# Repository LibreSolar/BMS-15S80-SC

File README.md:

# BMS48V
Battery management system for up to 15 Li-ion cells based on bq76940 or bq76930 IC from Texas Instruments

Please find a good description about system integration of the BMS in the [Open Source Ecology Wiki](https://wiki.opensourceecology.de/24-48V_BMS) (in German).

## Features (updated version 03/2022):
- implemented new plug (Würth 66202021022) to connect accumulator cells to PCB. This modification was necessary in order to ensure correct behaviour of measuring the cell voltage with BQ76940. Cell tap number C10 was dividied into C10/C10.1 and C5 into C5/C5.1.
- correct connection of CAN IC
- adapt board dimension to fit into following cap rail casing:
Apra Rail F06 open or M06 open 107*90*48 mm

ordering for example here:
https://www.reichelt.de/leergehaeuse-db6-fmh-
90-x-107-x-33-mm-apra-fo6-o-p251001.html?
&trstct=pos_3&nbc=1

## Features (updated version 10/2016):

- Up to 15 Li-ion cells (e.g. LiFePO4)
- Power circuit on separate board (see Switch-N-Sense repository)
- Balancing current approx. 150 mA
- STM32F072 ARM Cortex M0 microcontroller
- Built-in CAN communication interface and UEXT extension connector

## History

- Previous version was compatible to Arduino (based on ATmega 328P), but the processor was too small and didn't support CAN --> switched to STM32F072

(you can still find the old version by going back in the repository)

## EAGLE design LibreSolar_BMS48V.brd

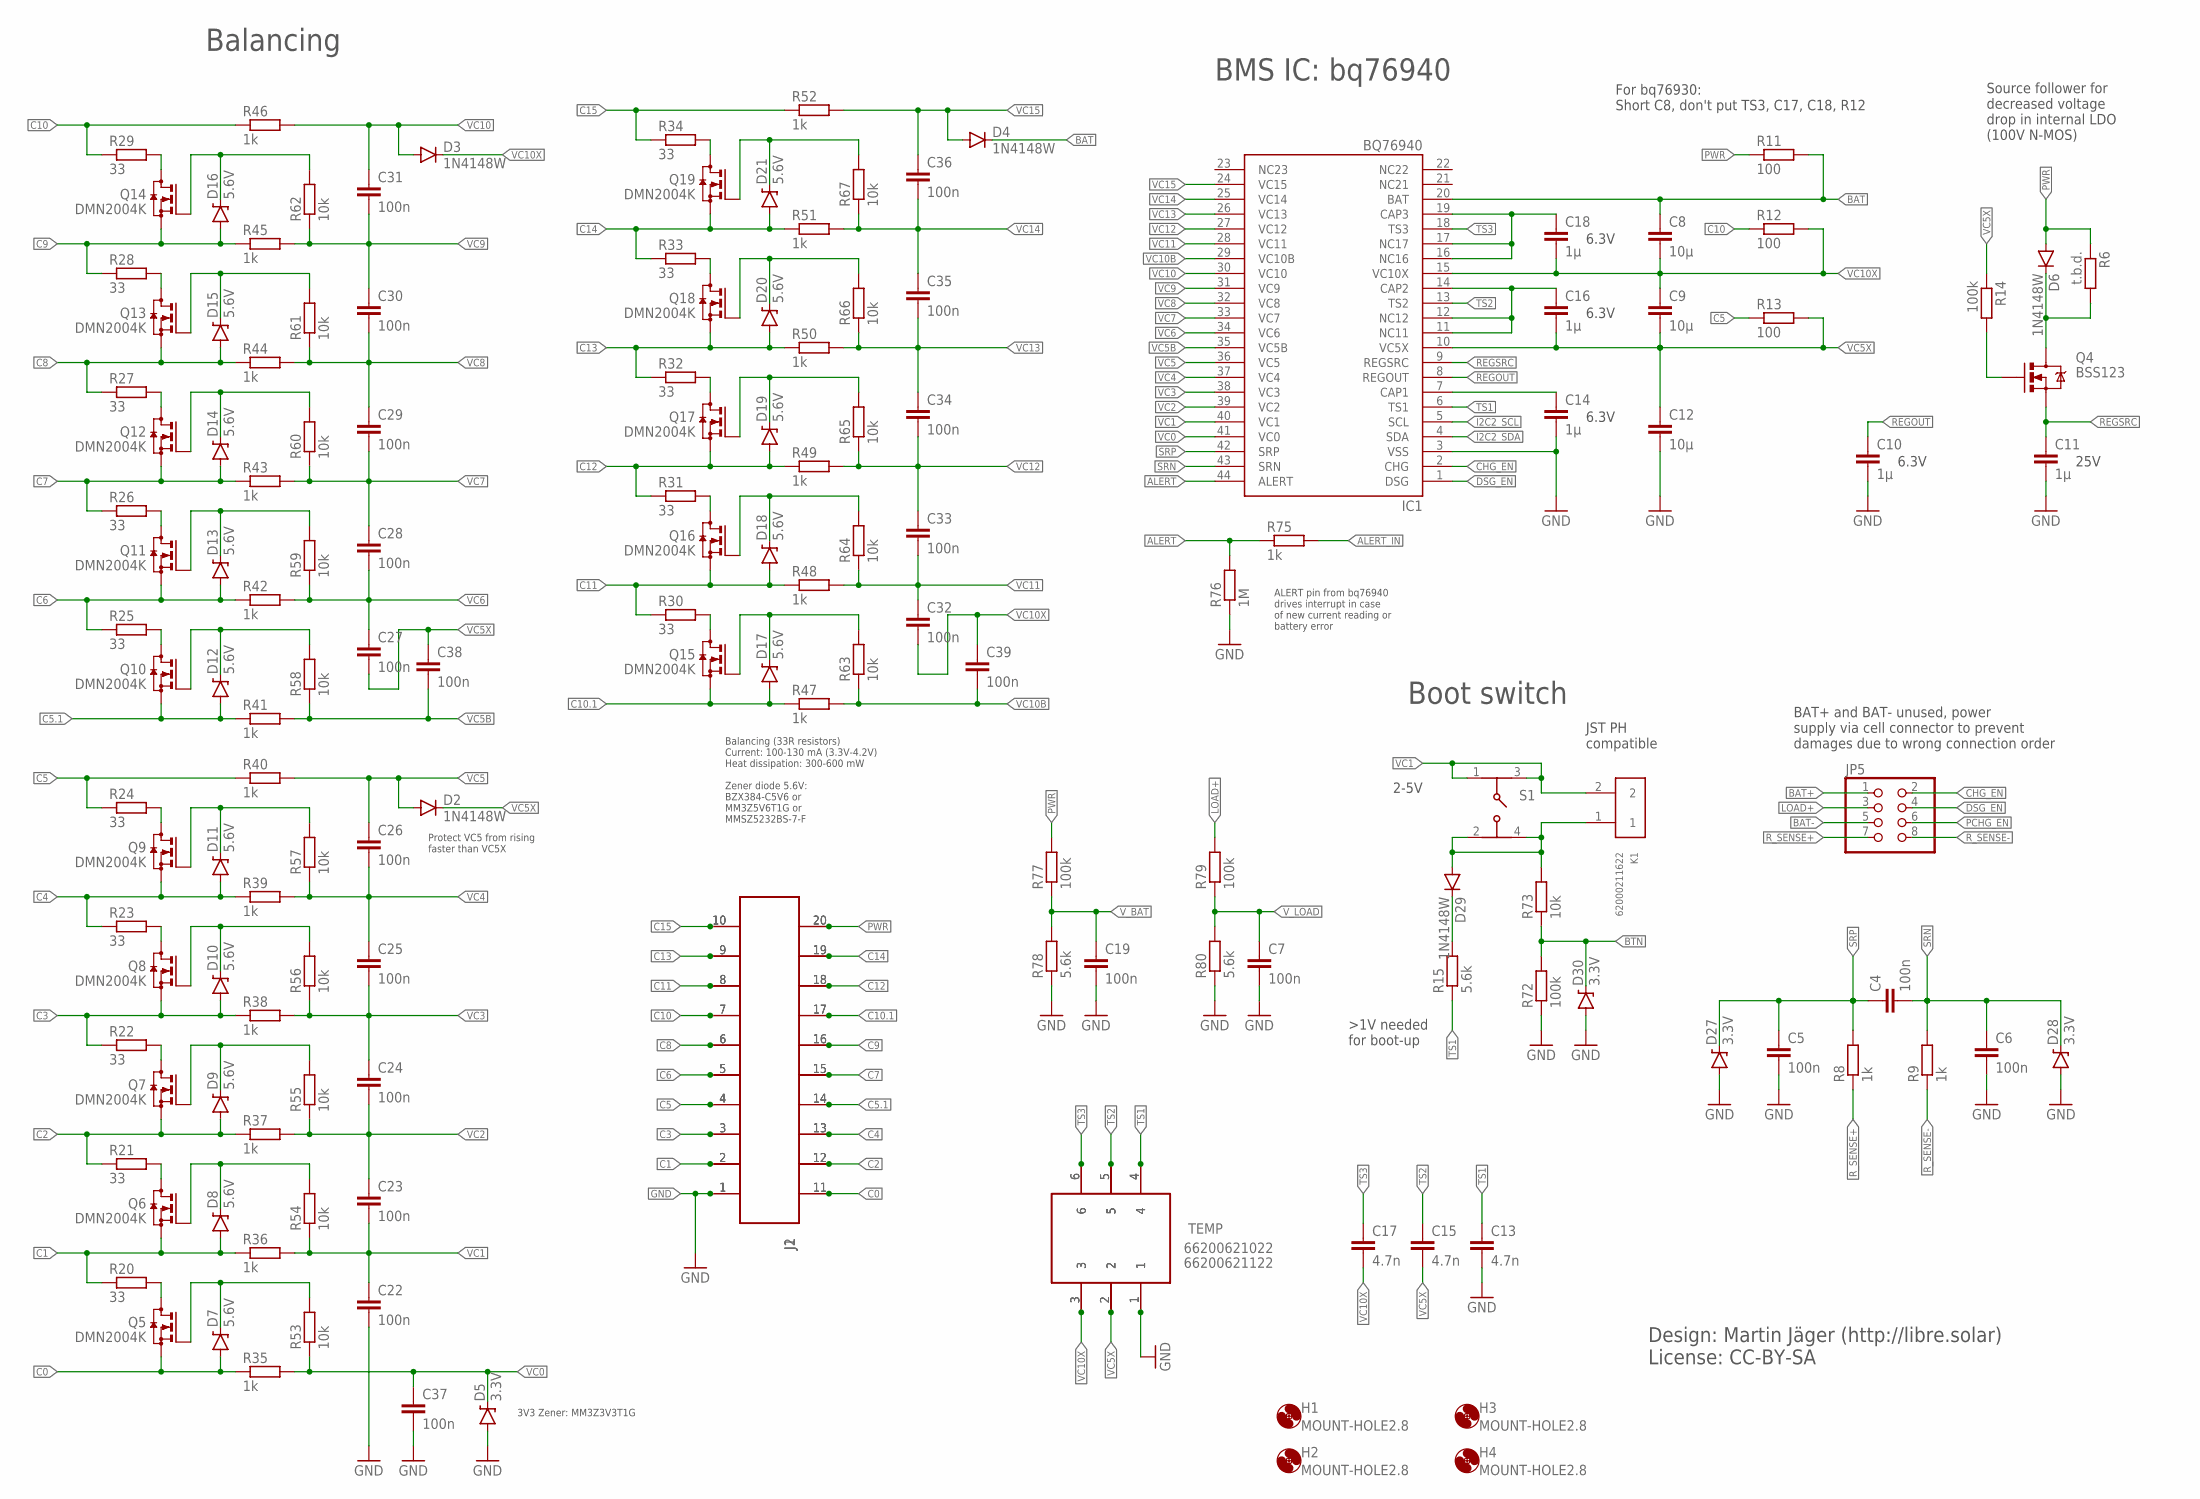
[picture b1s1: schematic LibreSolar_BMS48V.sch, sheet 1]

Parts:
C4, C5, C6, C7, C19, C22, C23, C24, C25, C26, C27, C28, C29, C30, C31, C32, C33, C34, C35, C36, C37, C38, C39: 100n; C0603; MPN 0603B104K500CT
C8, C9, C12: 10µ; C1210; MPN GRM32ER7YA106KA12L
C10: 1µ; C0603; MPN 0805YC475KAT2A
C11, C14, C16, C18: 1µ; C0603; MPN GRM188R71E105KA12D
C13, C15, C17: 4.7n; C0603; MPN 0603B104K500CT
D2, D3, D4, D6, D29: 1N4148W; SOD-123; MPN 1N4148W-7-F.
D5, D27, D28, D30: 3.3V; SOD-323; MPN BZX384-C5V6
D7, D8, D9, D10, D11, D12, D13, D14, D15, D16, D17, D18, D19, D20, D21: 5.6V; SOD-323; MPN BZX384-C5V6
H1, H2, H3, H4: MOUNT-HOLE2.8; 2,8
IC1: BQ76940; TSSOP44; MPN BQ7694003DBT
J1: 66202021122
J2: 66202021022
JP5: PINHD-2X4; 2X04
K1: 62000211622
K4: 66200621122
Q4: BSS123; SOT23-3; MPN 2N7002,215
Q5, Q6, Q7, Q8, Q9, Q10, Q11, Q12, Q13, Q14, Q15, Q16, Q17, Q18, Q19: DMN2004K; SOT23; MPN DMN2004K-7
R6: t.b.d.; R0603; MPN MCMR06X1001FTL
R8, R9, R35, R36, R37, R38, R39, R40, R41, R42, R43, R44, R45, R46, R47, R48, R49, R50, R51, R52, R75: 1k; R0603; MPN MCMR06X1001FTL
R11, R12, R13: 100; R0603; MPN MCMR06X1001FTL
R14: 100k; R0603
R15, R78, R80: 5.6k; R0603; MPN MCMR06X1001FTL
R20, R21, R22, R23, R24, R25, R26, R27, R28, R29, R30, R31, R32, R33, R34: 33; R2010; MPN ASC2010-33RFT4
R53, R54, R55, R56, R57, R58, R59, R60, R61, R62, R63, R64, R65, R66, R67: 10k; R0603; MPN ERJ3EKF1002V
R72, R77, R79: 100k; R0603; MPN MCMR06X1001FTL
R73: 10k; R0603; MPN MCMR06X1001FTL
R76: 1M; R0603; MPN ERJU06F1004V
S1: 430182050816
TEMP: 66200621022

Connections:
ALERT: IC1.44 (ALERT), R75.1, R76.2
ALERT_IN: R75.2; also elsewhere on the board
BAT: C8.1, D4.C, IC1.20 (BAT), R11.2
BAT+: JP5.1
BAT-: JP5.5
BTN: D30.C, R72.2, R73.1; also elsewhere on the board
C0: D7.A, J1.11, J2.11, Q5.2 (S), R35.1
C1: D8.A, J1.2, J2.2, Q6.2 (S), R20.1, R36.1
C2: D9.A, J1.12, J2.12, Q7.2 (S), R21.1, R37.1
C3: D10.A, J1.3, J2.3, Q8.2 (S), R22.1, R38.1
C4: D11.A, J1.13, J2.13, Q9.2 (S), R23.1, R39.1
C5: J1.4, J2.4, R13.1, R24.1, R40.1
C5.1: D12.A, J1.14, J2.14, Q10.2 (S), R41.1
C6: D13.A, J1.5, J2.5, Q11.2 (S), R25.1, R42.1
C7: D14.A, J1.15, J2.15, Q12.2 (S), R26.1, R43.1
C8: D15.A, J1.6, J2.6, Q13.2 (S), R27.1, R44.1
C9: D16.A, J1.16, J2.16, Q14.2 (S), R28.1, R45.1
C10: J1.7, J2.7, R12.1, R29.1, R46.1
C10.1: D17.A, J1.17, J2.17, Q15.2 (S), R47.1
C11: D18.A, J1.8, J2.8, Q16.2 (S), R30.1, R48.1
C12: D19.A, J1.18, J2.18, Q17.2 (S), R31.1, R49.1
C13: D20.A, J1.9, J2.9, Q18.2 (S), R32.1, R50.1
C14: D21.A, J1.19, J2.19, Q19.2 (S), R33.1, R51.1
C15: J1.10, J2.10, R34.1, R52.1
CAP1: C14.1, IC1.7 (CAP1)
CAP2: C16.1, IC1.11 (NC11), IC1.12 (NC12), IC1.14 (CAP2)
CAP3: C18.1, IC1.16 (NC16), IC1.17 (NC17), IC1.19 (CAP3)
CHG_EN: IC1.2 (CHG), JP5.2
DSG_EN: IC1.1 (DSG), JP5.4
GND: C5.2, C6.2, C7.2, C10.2, C11.2, C12.2, C13.2, C14.2, C19.2, C22.2, C37.2, D5.A, D27.A, D28.A, D30.A, IC1.3 (VSS), J1.1, J2.1, K4.1, R72.1, R76.1, R78.1, R80.1, TEMP.1; also elsewhere on the board
I2C2_SCL: IC1.5 (SCL); also elsewhere on the board
I2C2_SDA: IC1.4 (SDA); also elsewhere on the board
LOAD+: JP5.3, R79.2
MCU_IN: D29.A, K1.1, R73.2, S1.2, S1.4
unnamed: Q15.3 (D), R30.2
unnamed: Q16.3 (D), R31.2
unnamed: Q17.3 (D), R32.2
unnamed: D19.C, Q17.1 (G), R65.2
unnamed: Q6.3 (D), R21.2
unnamed: D18.C, Q16.1 (G), R64.2
unnamed: D7.C, Q5.1 (G), R53.2
unnamed: D29.C, R15.2
unnamed: D8.C, Q6.1 (G), R54.2
unnamed: D9.C, Q7.1 (G), R55.2
unnamed: Q5.3 (D), R20.2
unnamed: Q7.3 (D), R22.2
unnamed: D10.C, Q8.1 (G), R56.2
unnamed: Q8.3 (D), R23.2
unnamed: Q9.3 (D), R24.2
unnamed: D11.C, Q9.1 (G), R57.2
unnamed: D12.C, Q10.1 (G), R58.2
unnamed: Q10.3 (D), R25.2
unnamed: Q11.3 (D), R26.2
unnamed: D13.C, Q11.1 (G), R59.2
unnamed: D14.C, Q12.1 (G), R60.2
unnamed: Q12.3 (D), R27.2
unnamed: D15.C, Q13.1 (G), R61.2
unnamed: Q13.3 (D), R28.2
unnamed: Q14.3 (D), R29.2
unnamed: D16.C, Q14.1 (G), R62.2
unnamed: D17.C, Q15.1 (G), R63.2
unnamed: D20.C, Q18.1 (G), R66.2
unnamed: Q18.3 (D), R33.2
unnamed: D21.C, Q19.1 (G), R67.2
unnamed: Q19.3 (D), R34.2
unnamed: D6.C, Q4.3 (D), R6.2
unnamed: Q4.1 (G), R14.2
PCHG_EN: JP5.6; also elsewhere on the board
PWR: D6.A, J1.20, J2.20, R6.1, R11.1, R77.2; also elsewhere on the board
REGOUT: C10.1, IC1.8 (REGOUT); also elsewhere on the board
REGSRC: C11.1, IC1.9 (REGSRC), Q4.2 (S)
R_SENSE+: JP5.7, R8.1
R_SENSE-: JP5.8, R9.1
SRN: C4.2, C6.1, D28.C, IC1.43 (SRN), R9.2
SRP: C4.1, C5.1, D27.C, IC1.42 (SRP), R8.2
TS1: C13.1, IC1.6 (TS1), K4.4, R15.1, TEMP.4; also elsewhere on the board
TS2: C15.1, IC1.13 (TS2), K4.5, TEMP.5
TS3: C17.1, IC1.18 (TS3), K4.6, TEMP.6
VC0: C37.1, D5.C, IC1.41 (VC0), R35.2, R53.1
VC1: C22.1, C23.2, IC1.40 (VC1), K1.2, R36.2, R54.1, S1.1, S1.3
VC2: C23.1, C24.2, IC1.39 (VC2), R37.2, R55.1
VC3: C24.1, C25.2, IC1.38 (VC3), R38.2, R56.1
VC4: C25.1, C26.2, IC1.37 (VC4), R39.2, R57.1
VC5: C26.1, D2.A, IC1.36 (VC5), R40.2
VC5B: C38.2, IC1.35 (VC5B), R41.2, R58.1
VC5X: C9.2, C12.1, C15.2, C16.2, C27.2, C38.1, D2.C, IC1.10 (VC5X), K4.2, R13.2, R14.1, TEMP.2
VC6: C27.1, C28.2, IC1.34 (VC6), R42.2, R59.1
VC7: C28.1, C29.2, IC1.33 (VC7), R43.2, R60.1
VC8: C29.1, C30.2, IC1.32 (VC8), R44.2, R61.1
VC9: C30.1, C31.2, IC1.31 (VC9), R45.2, R62.1
VC10: C31.1, D3.A, IC1.30 (VC10), R46.2
VC10B: C39.2, IC1.29 (VC10B), R47.2, R63.1
VC10X: C8.2, C9.1, C17.2, C18.2, C32.2, C39.1, D3.C, IC1.15 (VC10X), K4.3, R12.2, TEMP.3
VC11: C32.1, C33.2, IC1.28 (VC11), R48.2, R64.1
VC12: C33.1, C34.2, IC1.27 (VC12), R49.2, R65.1
VC13: C34.1, C35.2, IC1.26 (VC13), R50.2, R66.1
VC14: C35.1, C36.2, IC1.25 (VC14), R51.2, R67.1
VC15: C36.1, D4.A, IC1.24 (VC15), R52.2
V_BAT: C19.1, R77.1, R78.2; also elsewhere on the board
V_LOAD: C7.1, R79.1, R80.2; also elsewhere on the board

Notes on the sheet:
Balancing (33R resistors) Current: 100-130 mA (3.3V-4.2V) Heat dissipation: 300-600 mW Zener diode 5.6V: BZX384-C5V6 or MM3Z5V6T1G or MMSZ5232BS-7-F
Balancing
BMS IC: bq76940
Design: Martin Jäger (http://libre.solar) License: CC-BY-SA
25V
6.3V
For bq76930: Short C8, don't put TS3, C17, C18, R12
Protect VC5 from rising faster than VC5X
Source follower for decreased voltage drop in internal LDO (100V N-MOS)
3V3 Zener: MM3Z3V3T1G
ALERT pin from bq76940 drives interrupt in case of new current reading or battery error
2-5V
BAT+ and BAT- unused, power supply via cell connector to prevent damages due to wrong connection order
Boot switch
JST PH compatible

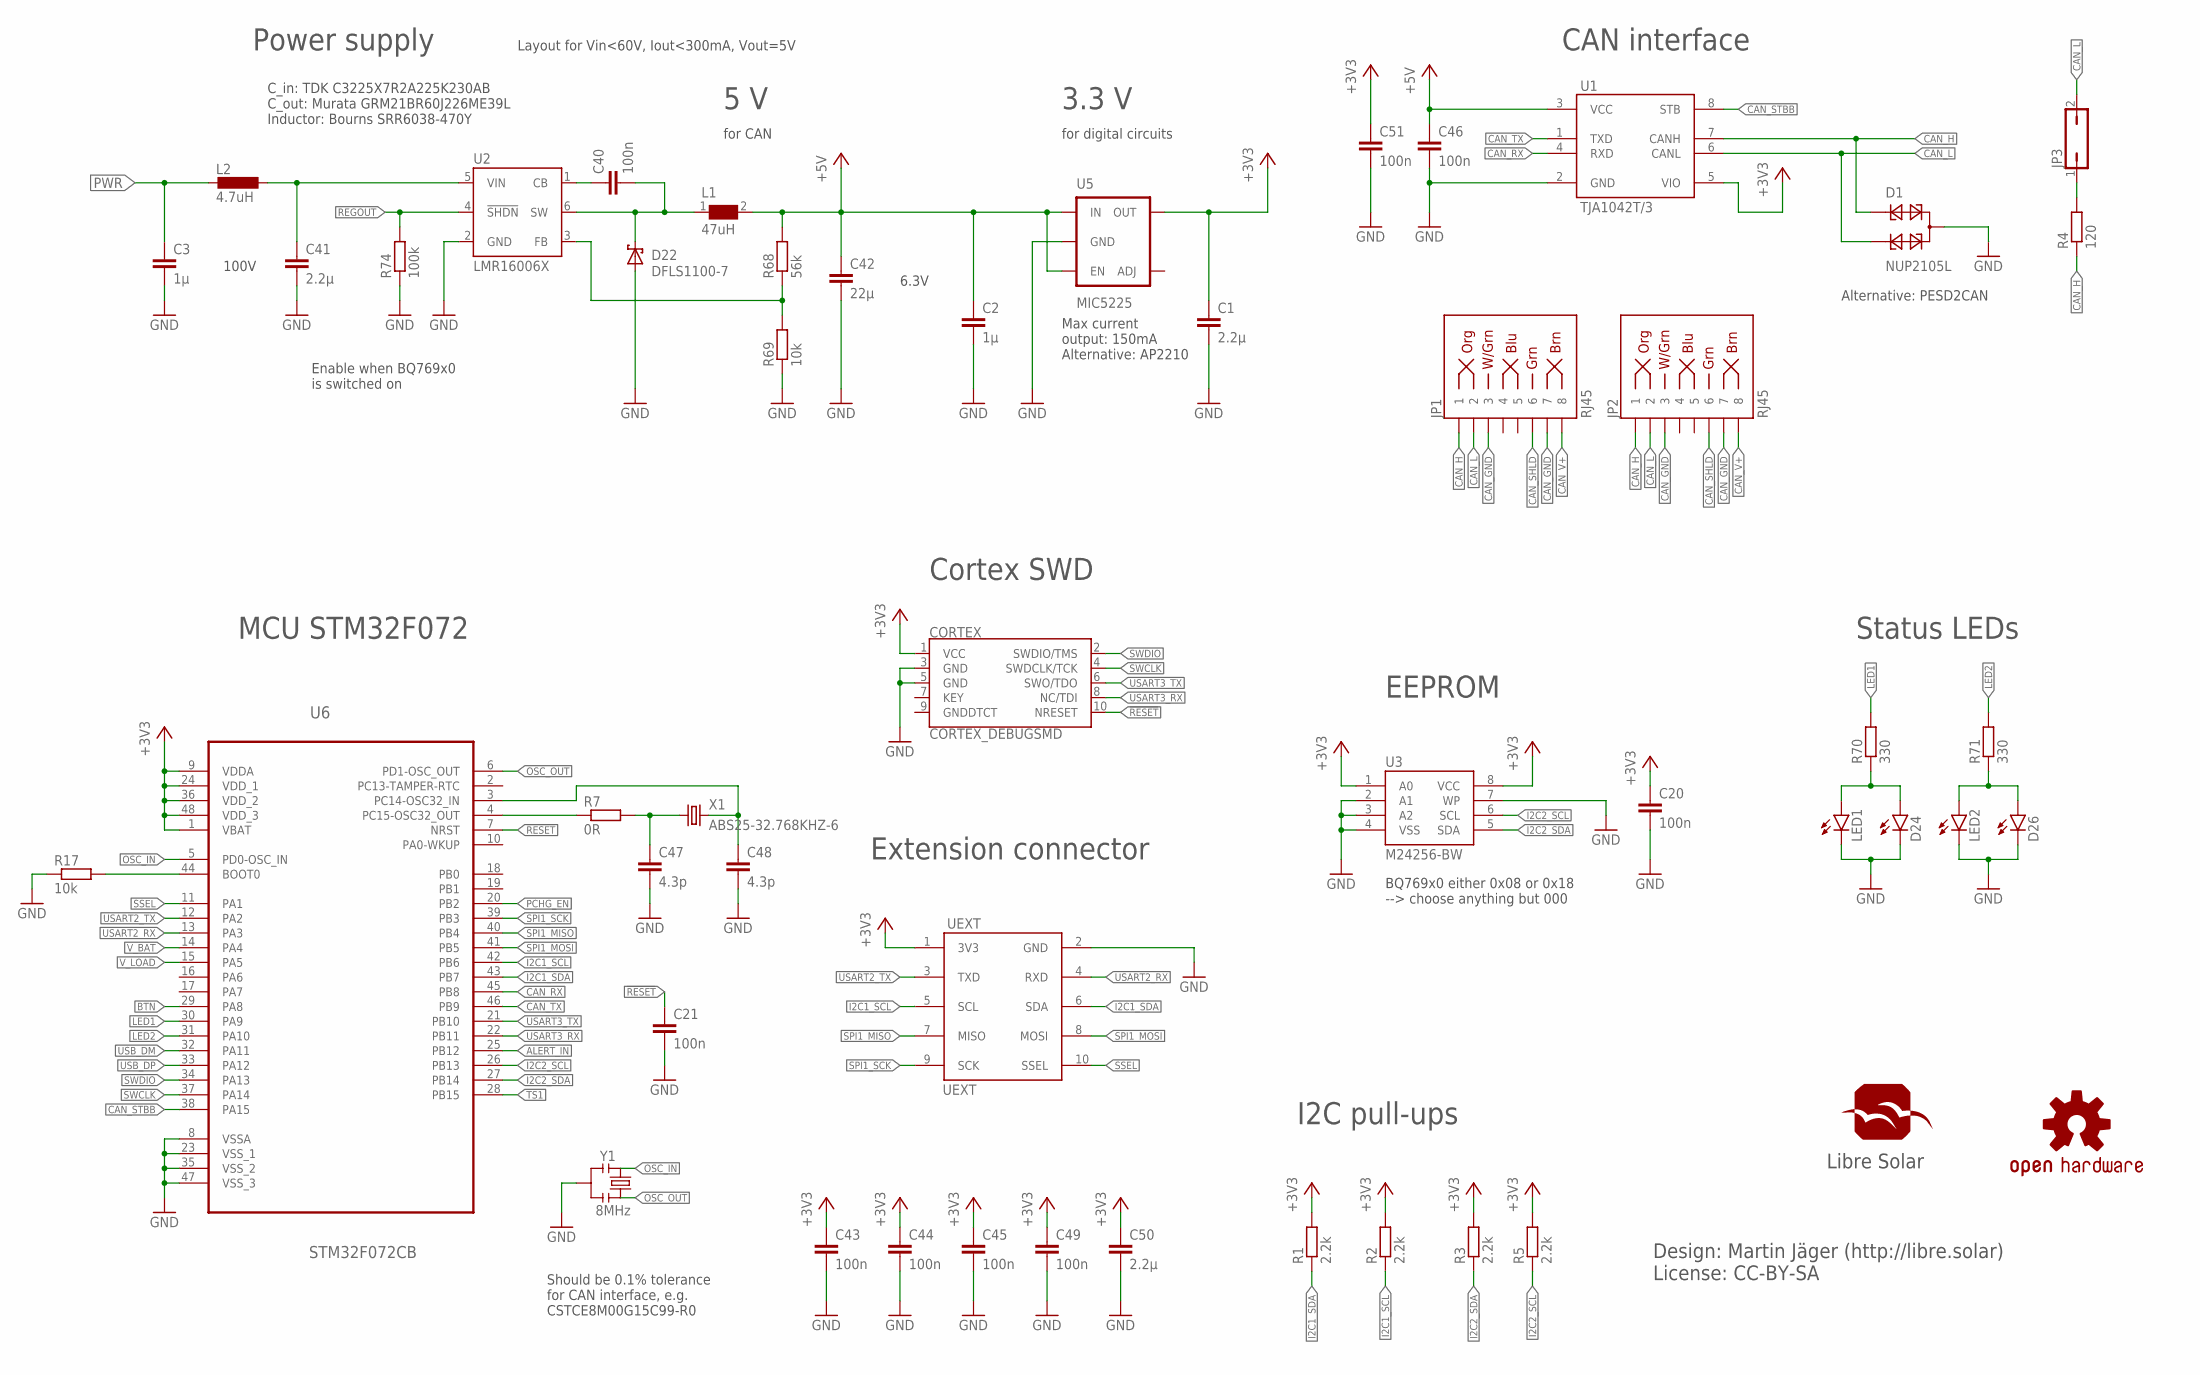
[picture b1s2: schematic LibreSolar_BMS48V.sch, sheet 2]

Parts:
C1, C50: 2.2µ; C0603; MPN 0805YC475KAT2A
C2: 1µ; C0603; MPN 08055C104KAT2A
C3: 1µ; C0805; MPN 08055C104KAT2A
C20, C21, C43, C44, C45, C49: 100n; C0603; MPN GRM188R71H104KA93D
C40: 100n; C0603; MPN 0603B104K500CT
C41: 2.2µ; C1210; MPN C3225X7R2A225K230AB
C42: 22µ; C0805; MPN GRM21BR60J226ME39L
C46, C51: 100n; C0603; MPN 06035C104KAT2A
C47, C48: 4.3p; C0603; MPN GRM188R71H104KA93D
CORTEX: CORTEX_DEBUGSMD; SAMTECH_FTSH-105-01
D1: NUP2105L; SOT23; MPN PESD2CAN
D22: DFLS1100-7; POWERDI123; MPN DFLS1100-7
D24, D26: LED0603; LED-0603
JP1, JP2: RJ45; RJ45-8; MPN RJHSE-5080
JP3: JP1Q; JP1
L1: 47uH; WE-TPC_6823
L2: 4.7uH; L2012C
LED1, LED2: LED3MM
N1: OSHW-LOGOM; OSHW-LOGO-M
R1, R2, R3, R5: 2.2k; R0603; MPN RC0603FR-072K2L.
R4: 120; R1206; MPN WCR0805-120RFI
R7: 0R; R0603; MPN RC0603FR-0710KL
R17: 10k; R0603; MPN RC0603FR-0710KL
R68: 56k; R0603; MPN CR0805-FX-1001ELF
R69: 10k; R0603; MPN ERJ3EKF1002V
R70, R71: 330; R0603; MPN MCMR06X1001FTL
R74: 100k; R0603; MPN ERJ3EKF1002V
U1: TJA1042T/3; SOIC-8-N
U2: LMR16006X; SOT23-6; MPN LMR16006XDDCT
U3: M24256-BW; SO08
U5: MIC5225; SOT23-5; MPN MIC5225-3.3YM5-TR
U6: STM32F072CB; QFP50P900X900X160-48N
U$1: LIBRESOLAR_LOGO
UEXT: UEXT
X1: ABS25-32.768KHZ-6; MM20SS
Y1: 8MHz; RESONATOR-SMD-1:1; MPN CSTCE8M00G15C99-R0

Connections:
!RESET: C21.1, CORTEX.10 (NRESET), U6.7 (NRST)
+3V3: C1.1, C20.1, C43.1, C44.1, C45.1, C49.1, C50.1, C51.1, CORTEX.1 (VCC), R1.2, R2.2, R3.2, R5.2, U1.5 (VIO), U3.1 (A0), U3.8 (VCC), U5.5 (OUT), U6.1 (VBAT), U6.9 (VDDA), U6.24 (VDD_1), U6.36 (VDD_2), U6.48 (VDD_3), UEXT.1 (3V3)
+5V: C2.1, C42.1, C46.1, L1.2, R68.2, U1.3 (VCC), U5.1 (IN), U5.3 (EN)
ALERT_IN: U6.25 (PB12); also elsewhere on the board
BTN: U6.29 (PA8); also elsewhere on the board
CAN_GND: JP1.3, JP1.7, JP2.3, JP2.7
CAN_H: D1.1, JP1.1, JP2.1, R4.1, U1.7 (CANH)
CAN_L: D1.2, JP1.2, JP2.2, JP3.2, U1.6 (CANL)
CAN_RX: U1.4 (RXD), U6.45 (PB8)
CAN_SHLD: JP1.6, JP2.6
CAN_STBB: U1.8 (STB), U6.38 (PA15)
CAN_TX: U1.1 (TXD), U6.46 (PB9)
CAN_V+: JP1.8, JP2.8
GND: C1.2, C2.2, C3.2, C20.2, C21.2, C41.2, C42.2, C43.2, C44.2, C45.2, C46.2, C47.2, C48.2, C49.2, C50.2, C51.2, CORTEX.3 (GND), CORTEX.5 (GND), D1.3, D22.A, D24.C, D26.C, LED1.K (C), LED2.K (C), R17.1, R69.1, R74.1, U1.2 (GND), U2.2 (GND), U3.2 (A1), U3.3 (A2), U3.4 (VSS), U3.7 (WP), U5.2 (GND), U6.8 (VSSA), U6.23 (VSS_1), U6.35 (VSS_2), U6.47 (VSS_3), UEXT.2 (GND), Y1.2; also elsewhere on the board
I2C1_SCL: R2.1, U6.42 (PB6), UEXT.5 (SCL)
I2C1_SDA: R1.1, U6.43 (PB7), UEXT.6 (SDA)
I2C2_SCL: R5.1, U3.6 (SCL), U6.26 (PB13); also elsewhere on the board
I2C2_SDA: R3.1, U3.5 (SDA), U6.27 (PB14); also elsewhere on the board
LED1: R70.2, U6.30 (PA9)
LED2: R71.2, U6.31 (PA10)
unnamed: C41.1, L2.1, U2.5 (VIN)
unnamed: R68.1, R69.2, U2.3 (FB)
unnamed: C40.2, D22.C, L1.1, U2.6 (SW)
unnamed: C40.1, U2.1 (CB)
unnamed: JP3.1, R4.2
unnamed: R7.1, U6.4 (PC15-OSC32_OUT)
unnamed: C47.1, R7.2, X1.1
unnamed: D24.A, LED1.A, R70.1
unnamed: C48.1, U6.3 (PC14-OSC32_IN), X1.4 (2)
unnamed: D26.A, LED2.A, R71.1
unnamed: R17.2, U6.44 (BOOT0)
OSC_IN: U6.5 (PD0-OSC_IN), Y1.1
OSC_OUT: U6.6 (PD1-OSC_OUT), Y1.3
PCHG_EN: U6.20 (PB2); also elsewhere on the board
PWR: C3.1, L2.2; also elsewhere on the board
REGOUT: R74.2, U2.4 (!SHDN!); also elsewhere on the board
SPI1_MISO: U6.40 (PB4), UEXT.7 (MISO)
SPI1_MOSI: U6.41 (PB5), UEXT.8 (MOSI)
SPI1_SCK: U6.39 (PB3), UEXT.9 (SCK)
SSEL: U6.11 (PA1), UEXT.10 (SSEL)
SWCLK: CORTEX.4 (SWDCLK/TCK), U6.37 (PA14)
SWDIO: CORTEX.2 (SWDIO/TMS), U6.34 (PA13)
TS1: U6.28 (PB15); also elsewhere on the board
USART2_RX: U6.13 (PA3), UEXT.4 (RXD)
USART2_TX: U6.12 (PA2), UEXT.3 (TXD)
USART3_RX: CORTEX.8 (NC/TDI), U6.22 (PB11)
USART3_TX: CORTEX.6 (SWO/TDO), U6.21 (PB10)
USB_DM: U6.32 (PA11)
USB_DP: U6.33 (PA12)
V_BAT: U6.14 (PA4); also elsewhere on the board
V_LOAD: U6.15 (PA5); also elsewhere on the board

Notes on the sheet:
C_in: TDK C3225X7R2A225K230AB C_out: Murata GRM21BR60J226ME39L Inductor: Bourns SRR6038-470Y
Layout for Vin<60V, Iout<300mA, Vout=5V
100V
6.3V
Power supply
Status LEDs
Design: Martin Jäger (http://libre.solar) License: CC-BY-SA
MCU STM32F072
Extension connector
CAN interface
I2C pull-ups
Alternative: PESD2CAN
Should be 0.1% tolerance for CAN interface, e.g. CSTCE8M00G15C99-R0
Cortex SWD
Max current output: 150mA Alternative: AP2210
3.3 V
for digital circuits
5 V
for CAN
Enable when BQ769x0 is switched on
BQ769x0 either 0x08 or 0x18 --> choose anything but 000
EEPROM

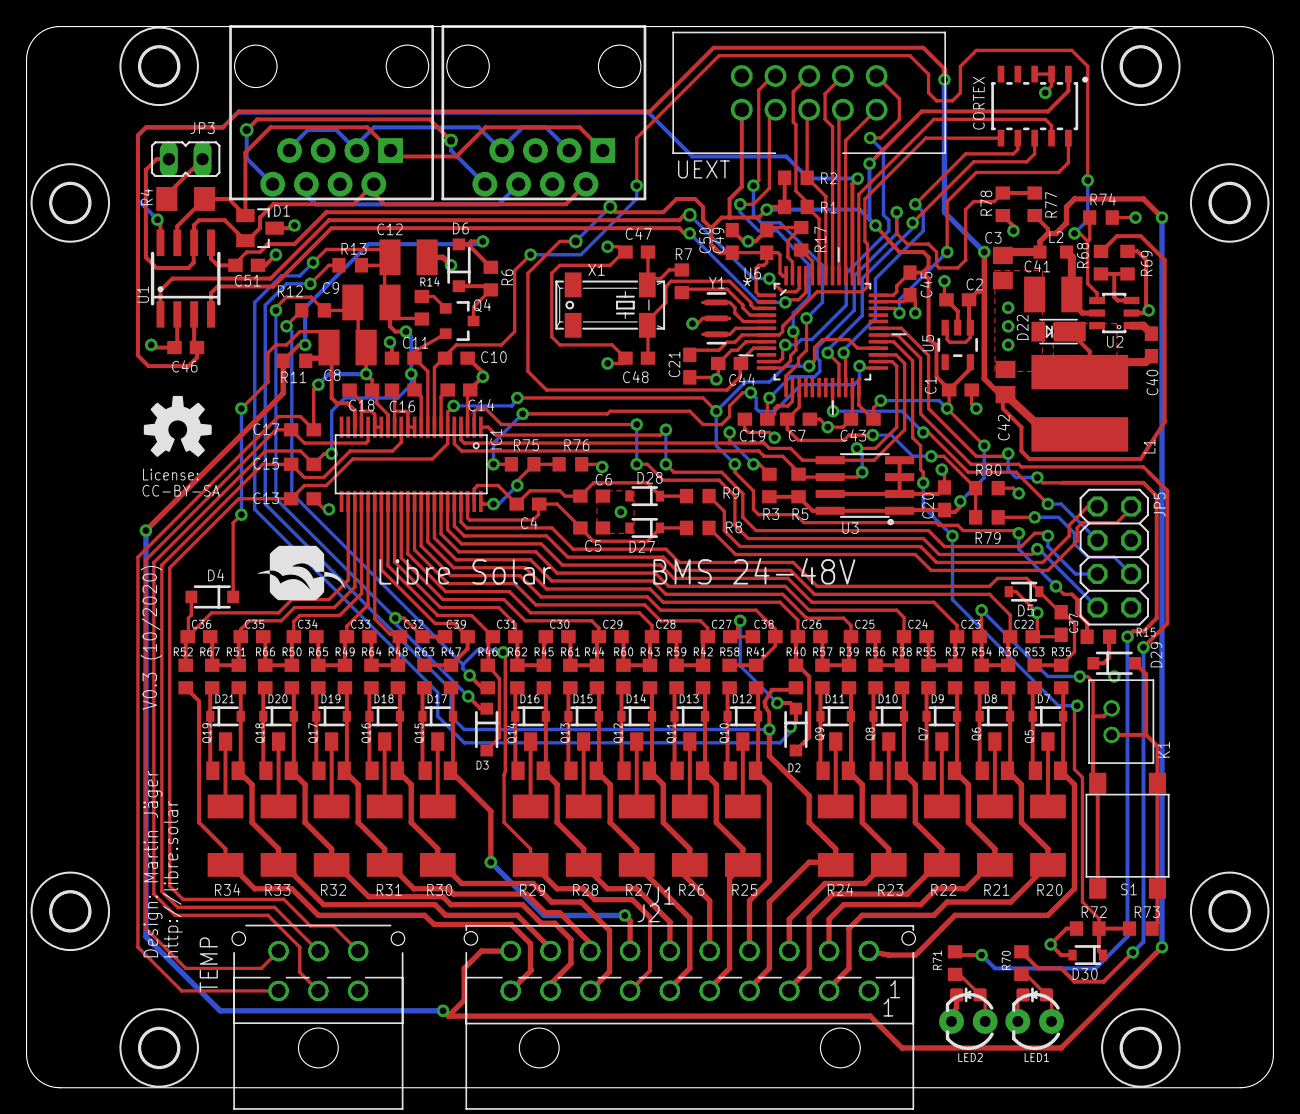
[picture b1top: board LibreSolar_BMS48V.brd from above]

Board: 8 copper layers, 94.0 x 80.0 mm, 205 parts (0 on the bottom side), 136 nets.

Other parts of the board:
H5, H6, H7, H8: MOUNT-HOLE2.8; 2,8

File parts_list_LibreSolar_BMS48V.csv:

Qty;Value;Device;Package;Parts;Description;MF;MPN;OC_FARNELL;Bemerkung
1;Spalte1;430182000000;430182050816;S1;6x6 mm SMD WS-TASV;Wurth Electronics Inc.;4301820508162;2065106;Spalte3
1;;66202021022;66202021022;J2;WR-MPC3 3.00mm Male Dual Row Angled Header with Plastic Pegs, 20 Pins=>Code : Con_WTB-MPC3_2_PCB_THT66202021022;WÜRTH ELECTRONICS;66202021022;2113446;
1;;;;;Stecker zu Buchse Würth 66202021022 - WR-MPC3 3.00 mm Female Dual Row Receptacle;WÜRTH ELECTRONICS;662020113322;2113501;Zubehör Anschluss der Platine
1;;JP1Q;JP1;JP3;JUMPER;AMPHENOL ICC;RJHSE-5080;1860577;nicht bestücken
1;;LED0603;LED-0603;D26;LEDs grün;Rohm;SML-D12P8WT86C;2687486;LED, 0603, Grün, Oberflächenmontage, 603, 20 mA, 2.2 V, 560 nm
1;;LED0603;LED-0603;D24;LEDs rot;Rohm;SML-D12V1WT86;3434721;LED, 0603, rot, Oberflächenmontage, 603, 20 mA, 2.2 V, 560 nm
2;;LED3MM;LED3MM;LED1, LED2;LEDs;BROADCOM;HLMP-Y502-F0000;1863180;nicht bestücken, Alternative zu SMD LED's
1;;PINHD-2X4;2X04;JP5;Stiftleiste, Wire-to-Board, 2.54 mm, 2 Reihe(n), 8 Kontakt(e), Durchsteckmontage;MULTICOMP PRO;MC-254-08-00-ST-DIP;2843526;
1;;;;;Stecker zur Stiftleiste, Wire-to-Board, 2.54 mm, 2 Reihe(n), 8 Kontakt(e), Durchsteckmontage;MULTICOMP PRO;MC-254-08-00-00-IDC;2843494;Zubehör Anschluss der Platine
1;0R;R-EU_R0603;R0603;R7;RESISTOR, European symbol;BOURNS;CR0603-J/-000ELF;2008343;
3;100;R-EU_R0603;R0603;R11, R12, R13;RESISTOR, European symbol;BOURNS;CR0603-FX-1000ELF;2008332;
1;100k;R-EU_R0603;R0603;R14;RESISTOR, European symbol;BOURNS;CR0603-FX-1003ELF;2008342;
3;100k;R-EU_R0603;R0603;R72, R77, R79;RESISTOR, European symbol;BOURNS;CR0603-FX-1003ELF;2008342;
1;100k;R-EU_R0603;R0603;R74;RESISTOR, European symbol;BOURNS;CR0603-FX-1003ELF;2008342;
2;100n;C-EUC0603;C0603;C46, C51;CAPACITOR, European symbol;AVX;06035C104KAT2A;1301804;
6;100n;C-EUC0603;C0603;C20, C21, C43, C44, C45, C49;CAPACITOR, European symbol;WALSIN;0603B104K500CT;2496834;
24;100n;C-EUC0603;C0603;C4, C5, C6, C7, C19, C22, C23, C24, C25, C26, C27, C28, C29, C30, C31, C32, C33, C34, C35, C36, C37, C38, C39, C40;CAPACITOR, European symbol;WALSIN;0603B104K500CT;2496834;
1;10k;R-EU_R0603;R0603;R73;RESISTOR, European symbol;BOURNS;CR0603-FX-1002ELF;2008341;
16;10k;R-EU_R0603;R0603;R53, R54, R55, R56, R57, R58, R59, R60, R61, R62, R63, R64, R65, R66, R67, R69;RESISTOR, European symbol;BOURNS;CR0603-FX-1002ELF;2008341;
1;10k;R-EU_R0603;R0603;R17;RESISTOR, European symbol;BOURNS;CR0603-FX-1002ELF;2008341;
3;10µ;C-EUC1210;C1210;C8, C9, C12;CAPACITOR, European symbol;MURATA;GRM32ER7YA106KA12L;2666606;
1;120;R-EU_R1206;R1206;R4;RESISTOR, European symbol;BOURNS;CR1206-FX-1200ELF;2333562;
1;1M;R-EU_R0603;R0603;R76;RESISTOR, European symbol;YAGEO  ;RC0603FR-071ML;9238840;
5;1N4148W;DIODESOD123;SOD-123;D2, D3, D4, D6, D29;Diode;DIODES INC.;1N4148W-7-F.;1776392;
21;1k;R-EU_R0603;R0603;R8, R9, R35, R36, R37, R38, R39, R40, R41, R42, R43, R44, R45, R46, R47, R48, R49, R50, R51, R52, R75;RESISTOR, European symbol;PANASONIC;ERJ3EKF1001V;2303145;
1;1µ;C-EUC0603;C0603;C10;CAPACITOR, European symbol;AVX;06033D105KAT2A;1658868;
1;1µ;C-EUC0603;C0603;C2;CAPACITOR, European symbol;AVX;06033D105KAT2A;1658868;
4;1µ;C-EUC0603;C0603;C11, C14, C16, C18;CAPACITOR, European symbol;AVX;06033D105KAT2A;1658868;
1;1µ;C-EUC0805;C0805;C3;CAPACITOR, European symbol;AVX;08055C105KAT2A;2094043;
4;2.2k;R-EU_R0603;R0603;R1, R2, R3, R5;RESISTOR, European symbol;BOURNS;CR0603-FX-2201ELF;2008338;
2;2.2µ;C-EUC0603;C0603;C1, C50;CAPACITOR, European symbol;AVX;06036D225KAT2A;1327678;
1;2.2µ;C-EUC1210;C1210;C41;CAPACITOR, European symbol;TDK;C3225X7R2A225K230AB;2112727;
1;22µ;C-EUC0805;C0805;C42;CAPACITOR, European symbol;MURATA;GRM21BR60J226ME39L;1735531;
4;3.3V;DIODE-ZENER5.6V;SOD-323;D5, D27, D28, D30;Zener Diode;NXP;BZX384-B3V3,115;2319335;
15;33;R-EU_R2010;R2010;R20, R21, R22, R23, R24, R25, R26, R27, R28, R29, R30, R31, R32, R33, R34;RESISTOR, European symbol;PANASONIC;ERJ12ZYJ330U;2323962;
2;330;R-EU_R0603;R0603;R70, R71;RESISTOR, European symbol;BOURNS;CR0603-FX-3300ELF;2908295;
2;4.3p;C-EUC0603;C0603;C47, C48;CAPACITOR, European symbol;MURATA;GRM1885C1H4R3CA01D ;Mouser:  81-GRM1885C1H4R3CA1D ;gibt’s nicht bei Farnell
3;4.7n;C-EUC0603;C0603;C13, C15, C17;CAPACITOR, European symbol;AVX;06035C472KAT2A;317263;
1;4.7uH;L-EUL2012C;L2012C;L2;INDUCTOR, European symbol;TDK;MLP2012S4R7MT;2345132;
1;47uH;WE-TPC_6823;WE-TPC_6823;L1;Shielded Tiny Power Inductor WE-TPC;BOURNS;SRR6038-470Y;2859255;
15;5.6V;DIODE-ZENER5.6V;SOD-323;D7, D8, D9, D10, D11, D12, D13, D14, D15, D16, D17, D18, D19, D20, D21;Zener Diode;ON SEMICONDUCTOR;MM3Z5V6T1G;1431204;
3;5.6k;R-EU_R0603;R0603;R15, R78, R80;RESISTOR, European symbol;BOURNS;CR0603-FX-5601ELF;2908322;
1;56k;R-EU_R0603;R0603;R68;RESISTOR, European symbol;BOURNS;CR0603-FX-5602ELF;2908323;
1;62000211622;62000211622;62000211622;K1;WR-WTB 2.00mm Male Vertical Shrouded Header, 2 Pins=>Code : Con_WTB_2.00_PCB_THT_62000211622;WÜRTH ELECTRONICS;62000211622;-;nicht bestücken
1;66200621022;66200621022;66200621022;TEMP;WR-MPC3 3.00mm Male Dual Row Angled Header with Plastic Pegs, 6 Pins=>Code : Con_WTB-MPC3_2_PCB_THT66200621022;WÜRTH ELECTRONICS;66200621022;1641823;Molex Anschluss Temperatur und Spannung Akku
1;;;;;Stecker zu Buchse Würth: 66200621022, WR-MPC3 3.00 mm Female Dual Row Receptacle 662006113322;WÜRTH ELECTRONICS;662006113322;1641835;Zubehör Anschluss der Platine
1;66200621122;66200621122;66200621122;K4;WR-MPC3 3.00mm Male Dual Row Vertical Header, 6 Pins=>Code : Con_WTB_MPC3_2_PCB_THT_66200621122;;;;Alternative Molex Anschluss Temperatur und Spannung Akku, nicht bestücken
1;8MHz;RESONATOR1:1;RESONATOR-SMD-1:1;Y1;Resonator;MURATA;CSTNE8M00GH5C000R0 ;Mouser:  81-CSTNE8M00GH5C000R ;gibt’s nicht bei Farnell
1;ABS25-32.768KHZ-6;CRYSTALMM20SS;MM20SS;X1;CRYSTAL;ABRACON;ABS25-32.768KHZ-6-1-T;2101353;
1;BQ76940;BQ76940;TSSOP44;IC1;;TEXAS INSTRUMENTS;BQ7694003DBT;3008763;
1;BSS123;MOSFET-NCHANNELBSS138;SOT23-3;Q4;Common NMOSFET Parts;ON SEMICONDUCTOR;BSS123;9845321;
1;CORTEX_DEBUGSMD;CORTEX_DEBUGSMD;SAMTECH_FTSH-105-01;CORTEX;Cortex Debug Connector;SAMTECH;FTSH-105-01-L-DV;1667759;
1;DFLS1100-7;SCHOTTKY-DIODEPOWERDI123;POWERDI123;D22;Schottky Diode;DIODES INC.;DFLS1100-7;1713889;
15;DMN2004K;DMN2004K;SOT23;Q5, Q6, Q7, Q8, Q9, Q10, Q11, Q12, Q13, Q14, Q15, Q16, Q17, Q18, Q19;N-CHANNEL MOS FET with low VGS and ESD protection;DIODES INC.;DMN2004K-7;1713842;
1;LMR16006X;LMR16006SOT-23;SOT23-6;U2;LMR16006 SIMPLE SWITCHERÂ® 60 V 0.6 A Buck Regulators With High Efficiency ECO Mode;TEXAS INSTRUMENTS;LMR16006XDDCT;2455133;
1;M24256-BW;EEPROM-I2CSMD;SO08;U3;I2C EEPROM chips, 24LC256 (and others);STM MICROELECTRONICS;M24256-BWMN6P;1224411;
1;MIC5225;V_REG_MIC5235;SOT23-5;U5;;MICROCHIP;MIC5225-3.3YM5-TR;2510262;
1;NUP2105L;PESD2CAN;SOT23;D1;CAN bus ESD protection diode;ON SEMICONDUCTOR;NUP2105LT1G;2101833;
2;RJ45;RJ45-8PTH;RJ45-8;JP1, JP2;RJ45 Jack;AMPHENOL COMMERCIAL PRODUCTS;RJHSE-5080;1860577;
1;STM32F072CB;STM32F072CB;QFP50P900X900X160-48N;U6;ARM-based 32-bit MCU;STM MICROELECTRONICS;STM32F072CBT6;2432094;
1;TJA1042T/3;TJA1042T/3;SOIC-8-N;U1;3.3V CAN transceiver;NXP;TJA1042T/3,118;2776119;
1;UEXT;UEXT;UEXT;UEXT;WR-BHD 2.54mm Male Box Header, 10 Pins=>Code : Con_WTB_BHD_2.54_Male_THT_WS_61201021621, ;MULTICOMP;MC-254-10-00-RA-DIP;2843542;
1;;;;;Stecker zu Buchse WR-BHD 2.54mm Male Box Header;MULTICOMP;MC-254-10-00-00-IDC;2843495;Zubehör Anschluss der Platine
1;t.b.d.;R-EU_R0603;R0603;R6;RESISTOR, European symbol;MULTICOMP;MCMR06X1001FTL;2073348;nicht bestücken

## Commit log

2016-03-05 Initial checkin of first board files
2016-03-25 Pinout of extension connector (LSX) changed
2016-10-03 Complete redesign with STM32F072 and external power part
2016-12-17 Uploaded image of assembled PCB
2016-12-17 Doc readme updated
2019-05-16 Link to documentation in OSE wiki added
2022-03-13 several modifications made for details see README.md

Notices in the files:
parts and their libraries:
PowerMagnetics: Copyright: Würth Elektronik
SparkFun-DiscreteSemi: Licensing: Creative Commons ShareAlike 4.0 International - https://creativecommons.org/licenses/by-sa/4.0
